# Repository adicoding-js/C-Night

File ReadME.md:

# C-Night

A handheld tactical HUD gadget built on an ESP32-S3. It combines a live camera feed, a thermal sensor, a laser pointer, and IR night vision into one device with an on-screen overlay.

## What it does

- Live camera feed (OV3660) pushed straight to an ILI9341 screen
- Thermal sensor (MLX90614) reads object temperature, shown as a HUD overlay
- Laser toggle button
- IR LED toggle for night vision
- HUD color cycle button (red / green / white)
- Shutter button (currently just beeps, no photo save yet)

# What does the firmware does:
- The firmware runs on an ESP32-S3 and drives four main systems: a live camera feed from the OV3660 sensor rendered directly to an ILI9341 display, a non-contact thermal readout from the MLX90614 overlaid on screen, a toggleable laser pointer and IR LED array for night vision, and a HUD color cycle for the on-screen crosshair and text. Button inputs handle all four toggles plus a shutter trigger, which currently only sounds a buzzer since photo/video saving isn’t implemented yet.
## Hardware

- ESP32-S3-DevKitC-1 (N8R8 or N16R8, needs PSRAM)
- OV3660 camera module
- MLX90614 thermal sensor
- ILI9341 TFT display
- Laser diode + IR LEDs
- 4x push buttons, buzzer

Custom PCB handles the laser, IR, thermal sensor, buttons, buzzer, and TFT wiring. Camera connects directly to the devkit.

# BOM

| Part | Specs | Source | Price (₹) | Qty | Link |
|---|---|---|---:|---:|---|
| ESP32-S3-DevKitC-1 | N8R8, 8 MB flash + 8 MB PSRAM | Robu | 1,389 | 1 | [Robu](https://robu.in/product/espressif-esp32-s3-devkitc-1-n8r8-development-board) |
| Camera module | OV3660; M5Stack Timer Camera, self-contained ESP32 + PSRAM camera | Robu | 1,779 | 1 | [Robu](https://robu.in/product/m5stack-esp32-psram-timer-camera-ov3660) |
| MLX90614 | GY-906 non-contact IR thermometer, I²C | Robu | 779 | 1 | [Robu](https://robu.in/?p=717378) |
| ILI9341 TFT | 2.8", SPI, 240×320 | Robu | 599–749 | 1 | [Robu](https://robu.in/?p=62026) |
| Laser diode module | 650 nm, 5 mW, 5 V | Robu | 10–32 | 1 | [Robu](https://robu.in/?p=16339) |
| IR emitter LEDs | 5 mm, 940 nm infrared transmitter LED | Amazon India | Under ₹150 per pack | 6 | Search Amazon: “5mm 940nm IR emitter LED pack” |
| AO3400 MOSFET | N-channel, SOT-23, 30 V / 5.8 A | Robu | Low-cost single unit | 1 | [Robu AO3400-HXY](https://robu.in/product/ao3400-hxy-mosfet-30v-5-8a-30m%25cf%258910v5-8a-1-4w-700mv-1-n-channel-sot-23-mosfets-rohs/) |
| S8050 transistor | NPN BJT, TO-92 package, 25 V / 500 mA | Robu | 3.70 | 3 | [Robu S8050 TO-92](https://robu.in/product/s8050range160-300-jcet-25v-625mw-160500ma1v-500ma-npn-to-92-3-bipolar-bjt-rohs/) |
| Buzzer | 5 V active electromagnetic buzzer, PCB mount | Robu | 11 | 1 | [Robu 5 V active buzzer](https://robu.in/product/5v-active-electromagnetic-buzzer-pack-of-5/) |
| Tactile push buttons | 12×12 mm, 4-pin, momentary, through-hole | Robocraze | Check product page | 4 | [Robocraze tactile buttons](https://robocraze.com/products/tactile-12x12x8mm-4-pin-push-button-switch-pack-of-5) |
| Resistors | 1/4 W metal-film assortment, 10 Ω–1 MΩ | Robu | Kit price on page | Misc | [Robu Plusivo resistor kit](https://robu.in/brand/plusivo/) |
| Capacitors | Ceramic + electrolytic component assortment | Robu | Kit price on page | Misc | [Robu component kits](https://robu.in/product-category/electronic-components/component-kits/) |

## Notes for BOM

- Use **IR emitter/transmitter LEDs**, not Robu’s 5 mm 940 nm IR receiver LED.
- The AO3400 is suitable for low-side switching of the IR LED string.
- The S8050 TO-92 version is easier to use on a breadboard than SOT-23.
- The buzzer listing is a pack of five; buy one pack and use one unit.
- The push-button listing is a pack of five; buy one pack and use four units.
- Buy resistors and capacitors as assortments rather than individual values.

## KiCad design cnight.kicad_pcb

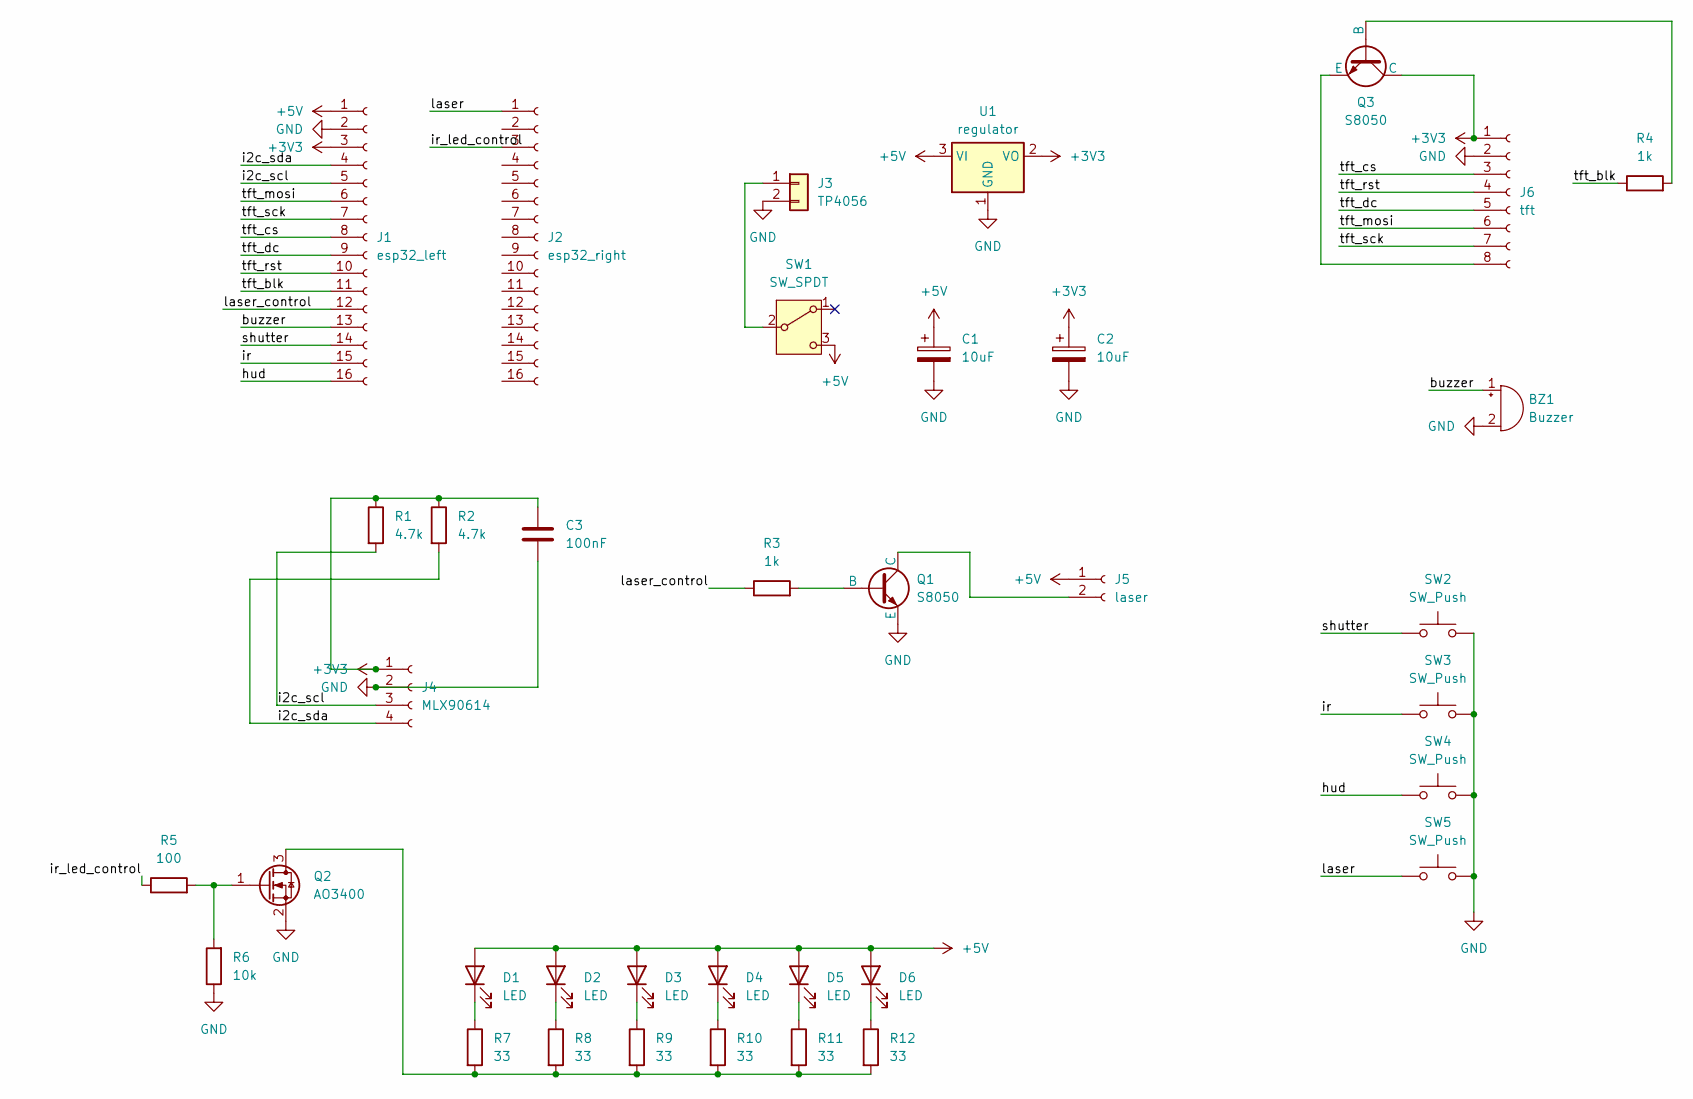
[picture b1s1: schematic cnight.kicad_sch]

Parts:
BZ1: Buzzer; Buzzer_12x9.5RM7.6
C1, C2: 10uF; CP_Radial_D5.0mm_P2.50mm
C3: 100nF; C_0805_2012Metric_Pad1.18x1.45mm_HandSolder
D1, D2, D3, D4, D5, D6: LED; LED_D5.0mm
J1: esp32_left; PinSocket_1x16_P2.54mm_Vertical
J2: esp32_right; PinSocket_1x16_P2.54mm_Vertical
J3: TP4056; PinHeader_1x02_P2.54mm_Vertical
J4: MLX90614; PinSocket_1x04_P2.54mm_Vertical
J5: laser; PinSocket_1x02_P2.54mm_Vertical
J6: tft; PinSocket_1x08_P2.54mm_Vertical
Q1, Q3: S8050; SOT-23
Q2: AO3400; SOT-23
R1, R2: 4.7k; R_0805_2012Metric_Pad1.20x1.40mm_HandSolder
R3, R4: 1k; R_0805_2012Metric_Pad1.20x1.40mm_HandSolder
R5: 100; R_0805_2012Metric_Pad1.20x1.40mm_HandSolder
R6: 10k; R_0805_2012Metric_Pad1.20x1.40mm_HandSolder
R7, R8, R9, R10, R11, R12: 33; R_0805_2012Metric_Pad1.20x1.40mm_HandSolder
SW1: SW_SPDT; PinHeader_1x03_P2.54mm_Vertical
SW2, SW3, SW4, SW5: SW_Push; SW_PUSH_6mm_H5mm
U1: regulator; SOT-223-3_TabPin2

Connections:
+3V3: C2.1, C3.1, J1.3, J4.1, J6.1, Q3.1 (C), R1.1, R2.1, U1.2 (VO)
+5V: C1.1, D1.2 (A), D2.2 (A), D3.2 (A), D4.2 (A), D5.2 (A), D6.2 (A), J1.1, J5.1, SW1.3 (C), U1.3 (VI)
/buzzer: BZ1.1 (+), J1.13
/hud: J1.16, SW4.1
/i2c_scl: J1.5, J4.3, R1.2
/i2c_sda: J1.4, J4.4, R2.2
/ir: J1.15, SW3.1
/ir_led_control: J2.3, R5.1
/laser: J2.1, SW5.1
/laser_control: J1.12, R3.1
/shutter: J1.14, SW2.1
/tft_blk: J1.11, R4.1
/tft_cs: J1.8, J6.3
/tft_dc: J1.9, J6.5
/tft_mosi: J1.6, J6.6
/tft_rst: J1.10, J6.4
/tft_sck: J1.7, J6.7
GND: BZ1.2 (-), C1.2, C2.2, C3.2, J1.2, J3.2, J4.2, J6.2, Q1.3 (E), Q2.2 (S), R6.1, SW2.2, SW3.2, SW4.2, SW5.2, U1.1 (GND)
unnamed: D1.1 (K), R7.1
unnamed: D2.1 (K), R8.1
unnamed: D3.1 (K), R9.1
unnamed: D4.1 (K), R10.1
unnamed: D5.1 (K), R11.1
unnamed: D6.1 (K), R12.1
unnamed: J3.1, SW1.2 (B)
unnamed: J5.2, Q1.1 (C)
unnamed: J6.8, Q3.3 (E)
unnamed: Q1.2 (B), R3.2
unnamed: Q2.3 (D), R7.2, R8.2, R9.2, R10.2, R11.2, R12.2
unnamed: Q2.1 (G), R5.2, R6.2
unnamed: Q3.2 (B), R4.2

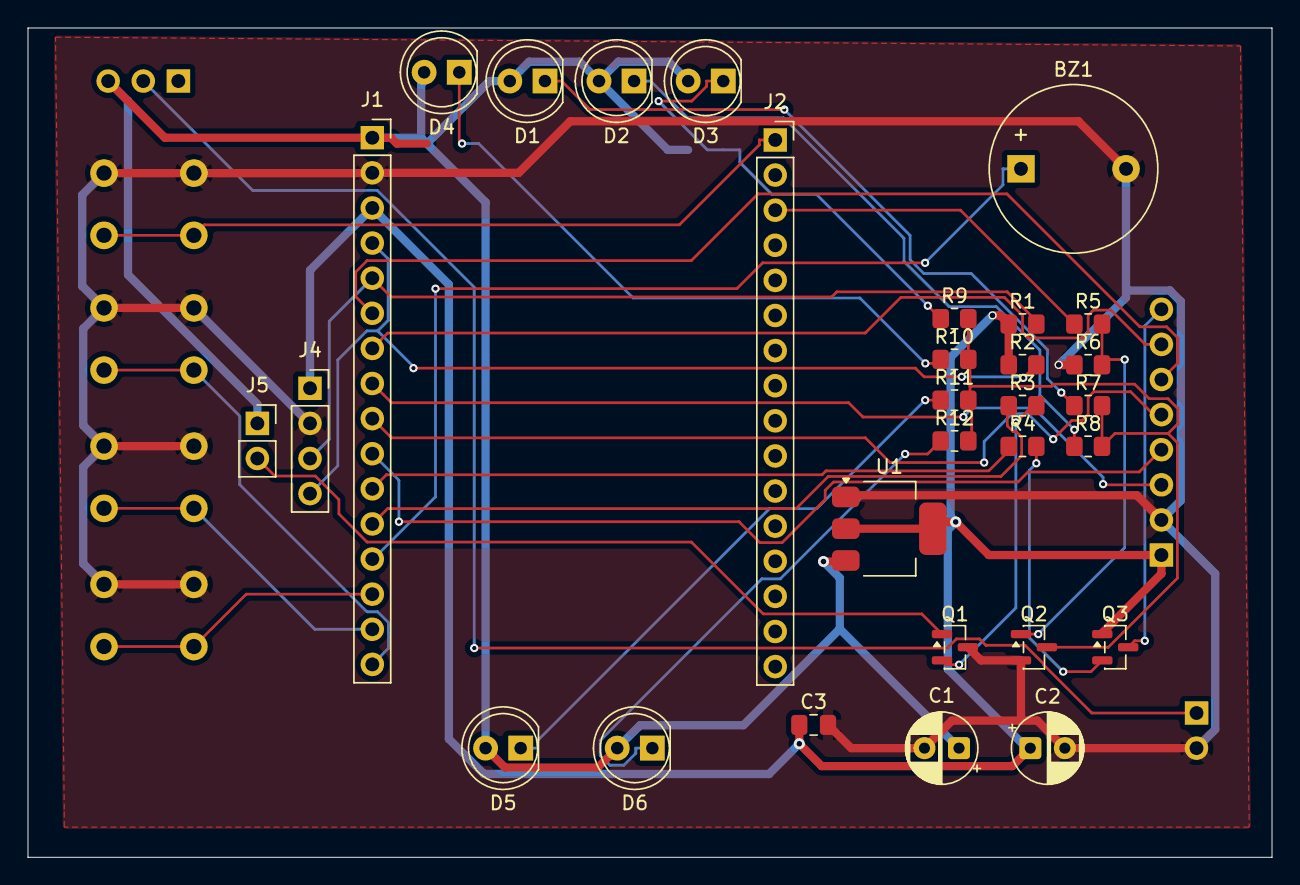
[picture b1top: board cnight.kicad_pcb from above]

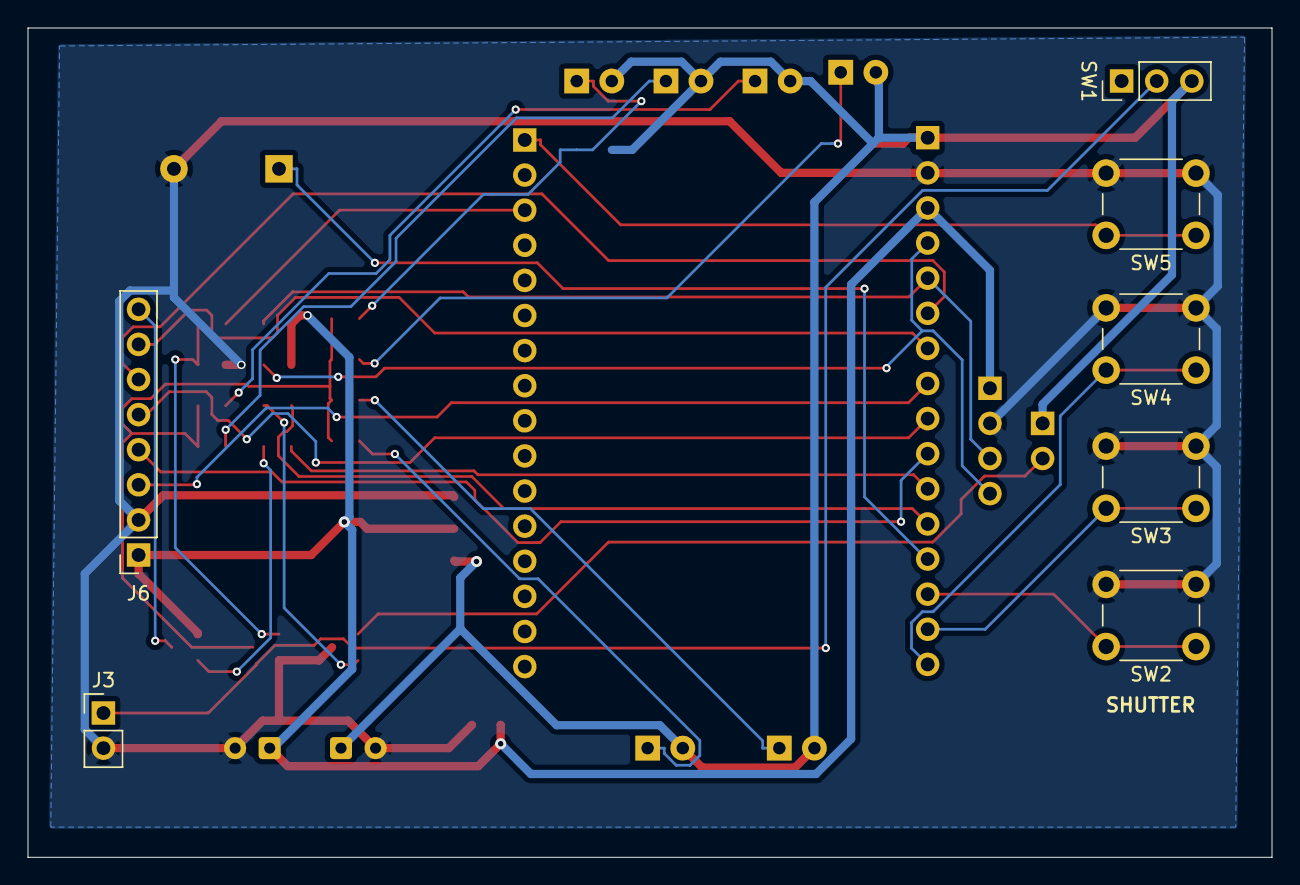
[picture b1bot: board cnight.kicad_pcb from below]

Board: 2 copper layers, 90.0 x 60.0 mm, 37 parts (7 on the bottom side), 31 nets.

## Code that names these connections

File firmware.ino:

#include "esp_camera.h"
#include <Wire.h>
#include <Adafruit_GFX.h>
#include <Adafruit_ILI9341.h>
#include <Adafruit_MLX90614.h>

Adafruit_MLX90614 therm = Adafruit_MLX90614();
Adafruit_ILI9341 tft = Adafruit_ILI9341(10, 13, 11, 12, 14);

int laser = 0;
int ir= 0;
  int hud_color_index = 0;
uint16_t hudcolors[3] = {ILI9341_RED, ILI9341_GREEN, ILI9341_WHITE};

unsigned long lastDebounce = 0;

void setup() {
  Serial.begin(115200);
pinMode(1, OUTPUT); // laser_control
pinMode(2, OUTPUT); // ir_led_control
pinMode(42, OUTPUT); // buzzer
pinMode(21, OUTPUT); // tft_blk

pinMode(4, INPUT_PULLUP); // shutter
pinMode(5, INPUT_PULLUP); // ir btn
pinMode(6, INPUT_PULLUP); // hud btn
pinMode(7, INPUT_PULLUP); // laser btn

digitalWrite(1, LOW);
digitalWrite(2, LOW);
digitalWrite(21, HIGH);

tft.begin();
tft.setRotation(1);
tft.fillScreen(ILI9341_BLACK);

  Wire.begin(8, 9);
  if (!therm.begin()) {
Serial.println("mlx problem");
  }

camera_config_t config;
config.ledc_channel = LEDC_CHANNEL_0;
config.ledc_timer = LEDC_TIMER_0;
config.pin_d0 = 38;
config.pin_d1 = 39;
config.pin_d2 = 40;
config.pin_d3 = 41;
config.pin_d4 = 47;
config.pin_d5 = 48;
config.pin_d6 = 33;
config.pin_d7 = 34;
config.pin_xclk = 15;
config.pin_pclk = 16;
config.pin_vsync = 17;
config.pin_href = 18;
config.pin_sccb_sda = 8;
config.pin_sccb_scl = 9;
config.pin_pwdn = -1;
config.pin_reset = -1;
config.xclk_freq_hz = 20000000;
config.pixel_format = PIXFORMAT_RGB565;
config.frame_size = FRAMESIZE_QVGA;
config.jpeg_quality = 12;
config.fb_count = 1;

  if (psramFound()) {
config.fb_count = 2;
  }

  esp_err_t err = esp_camera_init(&config);
if (err != ESP_OK) {
    Serial.printf("cam init failed 0x%x", err);
  }
}

void loop() {

if (millis() - lastDebounce > 250) {
    if (digitalRead(7) == LOW) { 
  laser = !laser;
      digitalWrite(1, laser ? HIGH : LOW);
    lastDebounce = millis();
}
if (digitalRead(5) == LOW) { 
      ir = !ir;
  digitalWrite(2, ir ? HIGH : LOW);
    lastDebounce = millis();
    }

if (digitalRead(6) == LOW) { 
hud_color_index = hud_color_index + 1;
      if (hud_color_index > 2) {
    hud_color_index = 0;
}
  lastDebounce = millis();
    }

    if (digitalRead(4) == LOW) { 
  digitalWrite(42, HIGH);
      delay(100);
digitalWrite(42, LOW);
    lastDebounce = millis();
    }
  }
  camera_fb_t *fb = esp_camera_fb_get();
  if (!fb) {
Serial.println("cam capture failed");
    return;
  }
  tft.drawRGBBitmap(0, 0, (uint16_t *)fb->buf, 320, 240);
  esp_camera_fb_return(fb);

float objTemp = therm.readObjectTempC();
uint16_t activeColor = hudcolors[hud_color_index];

tft.drawCircle(160, 120, 15, activeColor);
tft.drawLine(160, 100, 160, 140, activeColor);
tft.drawLine(140, 120, 180, 120, activeColor);

tft.setCursor(10, 10);
tft.setTextSize(3);
tft.setTextColor(activeColor);
tft.print("TEMP: ");
tft.print(objTemp, 1);
  tft.print(" C");

tft.setTextSize(2);
tft.setCursor(10, 210);
  if (laser) {
tft.print("[LASER] ");
  }
if (ir) {
    tft.print("[NIGHT_VISION]");
  }
}
